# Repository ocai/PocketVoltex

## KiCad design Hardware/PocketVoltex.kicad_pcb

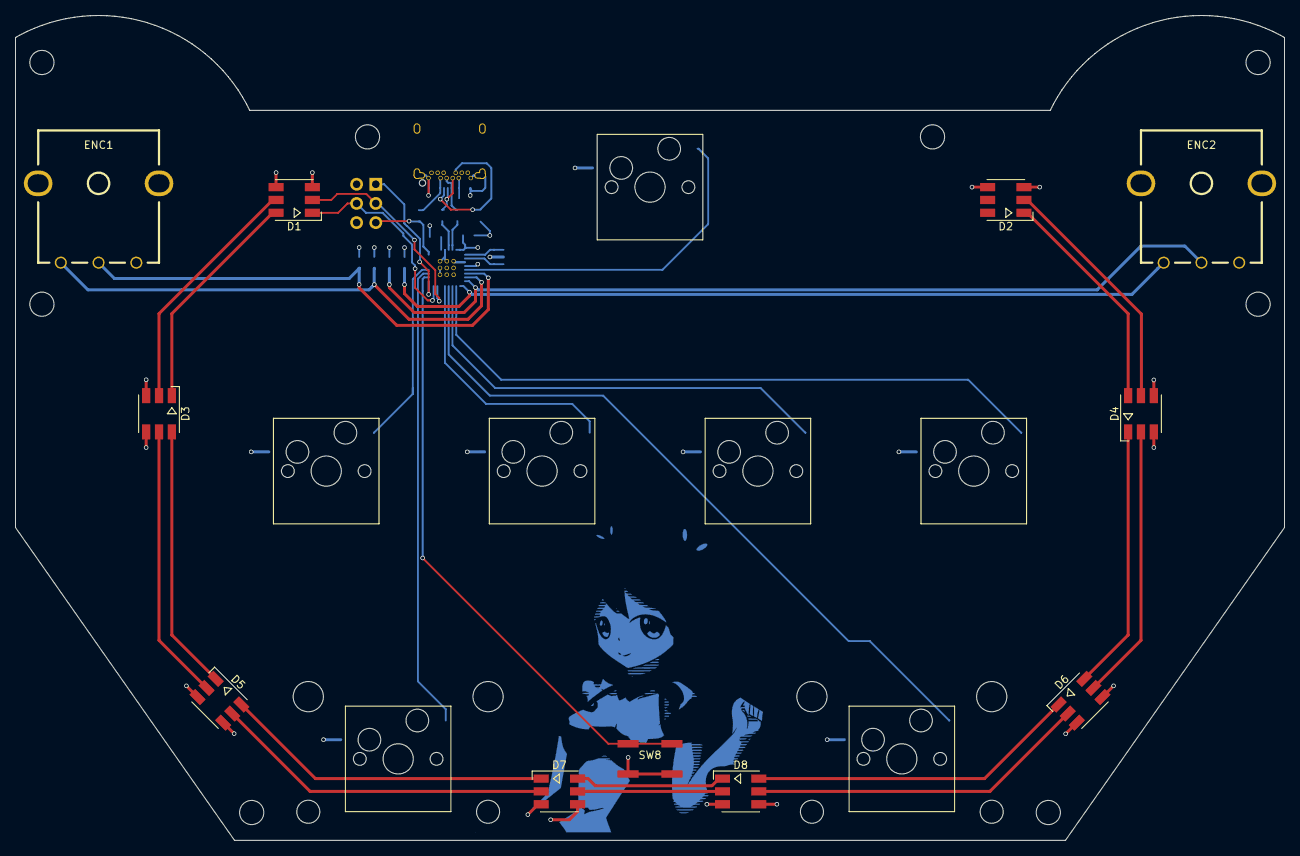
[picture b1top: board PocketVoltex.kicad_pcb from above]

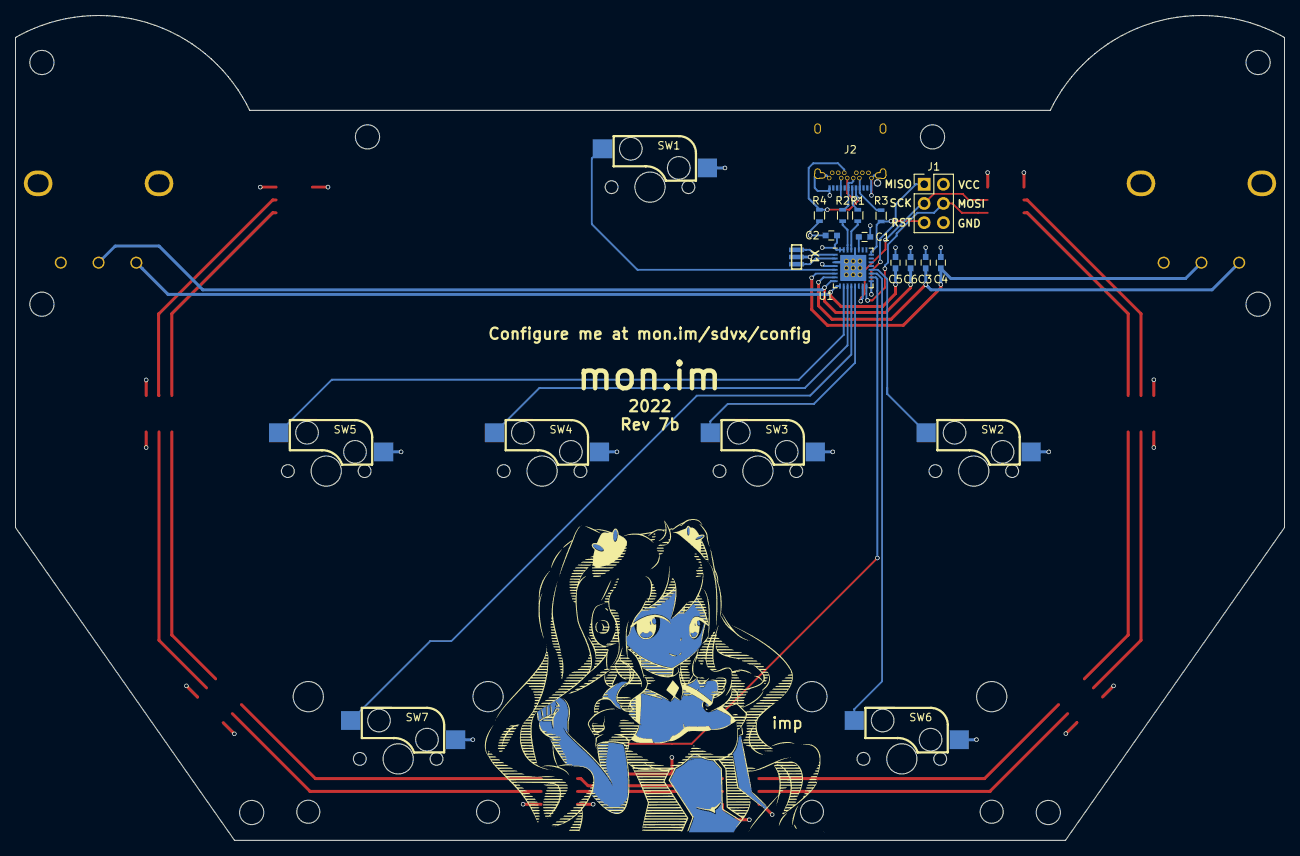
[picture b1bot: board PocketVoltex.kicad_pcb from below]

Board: 4 copper layers, 168.0 x 109.2 mm, 32 parts (14 on the bottom side), 40 nets.

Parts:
C1: 1uF; C_0603
C2: 10uF; C_0603
C3, C4, C5, C6: 10nF; C_0603
D1, D2, D3, D4, D5, D6, D7, D8: SK9822; LED_SK9822
ENC1: VOL_L; Encoder_Bourns_PEC16
ENC2: VOL_R; Encoder_Bourns_PEC16
J1: Programming header; Pin_Header_Straight_2x03_Pitch2.54mm
J2: USB_C_Receptacle; USB_C_Receptacle_UJ31-CH-31-SMT-TR
R1, R2: 22R; R_0603
R3: 10k; R_0603
R4: 5.1k; R_0603
SW1: MX socket; SW_Cherry_MX1A_1.00u_PCB_Socket
SW2, SW3, SW4, SW5: MX socket; SW_Cherry_MX1A_1.25u_PCB_Socket
SW6, SW7: MX socket; SW_Cherry_MX1A_2.25u_PCB_Socket
SW8: SW_Push; SW_SPST_KSC-J
U1: ATMEGA16U2-AU; QFN-32-1EP_5x5mm_Pitch0.5mm
X1: 16MHz; murata-resonator_SMD_CSTCE16M0V53-R0

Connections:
/D+: J2.A6 (D+), J2.B6 (D+), R1.1
/D-: J2.A7 (D-), J2.B7 (D-), R2.2
/ENC1A: C3.1, U1.7 ((AIN0/INT1)PD1)
/ENC1B: C4.2, U1.6 ((OC.0B/INT0)PD0)
/ENC2A: C5.1, U1.9 ((TXD1/INT3)PD3)
/ENC2B: C6.2, U1.8 ((RXD1/AIN1/INT2)PD2)
/MISO: J1.1, U1.17 ((PD0/MISO/PCINT3)PB3)
/MOSI: D1.1 (SDI), J1.4, U1.16 ((PDI/MOSI/PCINT2)PB2)
/RESET: J1.5, R3.2, U1.24 (PC1(~RESET/dW))
/SCLK: D1.2 (CKI), J1.3, U1.15 ((SCLK/PCINT1)PB1)
/SW_A: SW2.1, U1.20 ((PCINT6)PB6)
/SW_B: SW3.1, U1.13 ((~CTS/~HWB/AIN6/T0/INT7)PD7)
/SW_C: SW4.1, U1.11 ((XCK/AIN4/PCINT12)PD5)
/SW_D: SW5.1, U1.10 ((INT5/AIN3)PD4)
/SW_FXL: SW6.1, U1.19 ((PCINT5)PB5)
/SW_FXR: SW7.1, U1.12 ((~RTS/AIN5/INT6)PD6)
/SW_MACRO: SW8.1, U1.18 ((T1/PCINT4)PB4)
/SW_START: SW1.1, U1.5 ((PCINT11/AIN2)PC2)
GND: C1.1, C2.2, C3.2, C4.1, C5.2, C6.1, D1.3 (GND), D2.3 (GND), D3.3 (GND), D4.3 (GND), D5.3 (GND), D6.3 (GND), D7.3 (GND), D8.3 (GND), ENC1.2, ENC2.2, J1.6, J2.A1 (GND), J2.A12 (GND), J2.B1 (GND), J2.B12 (GND), J2.S1 (SHIELD), R4.1, SW1.2, SW2.2, SW3.2, SW4.2, SW5.2, SW6.2, SW7.2, SW8.2, U1.3 (GND), U1.28 (UGND), X1.2
unnamed: C1.2, U1.27 (UCAP)
unnamed: D1.5 (CKO), D3.2 (CKI)
unnamed: D1.6 (SDO), D3.1 (SDI)
unnamed: D2.1 (SDI), D4.6 (SDO)
unnamed: D2.2 (CKI), D4.5 (CKO)
unnamed: D3.5 (CKO), D5.2 (CKI)
unnamed: D3.6 (SDO), D5.1 (SDI)
unnamed: D4.1 (SDI), D6.6 (SDO)
unnamed: D4.2 (CKI), D6.5 (CKO)
unnamed: D5.5 (CKO), D7.2 (CKI)
unnamed: D5.6 (SDO), D7.1 (SDI)
unnamed: D6.1 (SDI), D8.6 (SDO)
unnamed: D6.2 (CKI), D8.5 (CKO)
unnamed: D7.5 (CKO), D8.2 (CKI)
unnamed: D7.6 (SDO), D8.1 (SDI)
unnamed: J2.A5 (CC1), J2.B5 (CC2), R4.2
unnamed: R1.2, U1.29 (D+)
unnamed: R2.1, U1.30 (D-)
unnamed: U1.1 (XTAL1), X1.1
unnamed: U1.2 (PC0(XTAL2)), X1.3
VCC: C2.1, D1.4 (VCC), D2.4 (VCC), D3.4 (VCC), D4.4 (VCC), D5.4 (VCC), D6.4 (VCC), D7.4 (VCC), D8.4 (VCC), J1.2, J2.A4 (VBUS), J2.A9 (VBUS), J2.B4 (VBUS), J2.B9 (VBUS), R3.1, U1.4 (VCC), U1.31 (UVCC), U1.32 (AVCC)

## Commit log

2021-06-02 rev7a - Added pulldown resistors to rev7 artwork
2022-04-30 rev7b - Updated layout to 4 layers
